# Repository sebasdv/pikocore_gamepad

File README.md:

# pikocore — RP2350-PiZero + GamePi13 port

A community port of [pikocore](https://github.com/schollz/pikocore), the hackable
open-source lo-fi sampler, to run on the **Waveshare RP2350-PiZero** paired with the
**GamePi13** handheld HAT — trading the original's bare-bones potentiometer interface
for a 240×240 color LCD dashboard and a 12-button game-console layout.

This is an independent fork, not officially affiliated with the original pikocore
project or with Waveshare.

## What's different from stock pikocore

- **Full-color 240×240 LCD dashboard** — BPM, clock source, sample name/index,
  live waveform with playhead and per-slice highlighting, the active parameter's
  value as a segmented bar, and the current mode.
- **12 physical buttons** (D-pad + Y/X/B/A + Select/Start/L/R) replace the original's
  8 buttons + 3 potentiometers, with a full on-screen menu system to reach every
  parameter without needing analog knobs.
- **Save/Load device state to flash** — one persisted slot covering every parameter,
  the sequencer pattern, and each mode's own knob position, with on-screen
  save/load confirmation icons.
- **Onboard step sequencer** with visible record/play/clear feedback instead of a
  blind knob.
- **USB bank-loader web app** (React + Vite, in `web/`) to build `.pikobank` files
  from your own samples and load them straight over USB.
- **MIDI clock and transport over USB** — start, stop, continue and clock from a
  computer or phone sync the sequencer, in either clock-input mode.
- microSD `.pikobank` browsing exists in the codebase but ships **disabled by
  default** behind a build flag (`PIKO_GAMEPI13_SD`) — see
  [GAMEPI13-INTERFACE.md](GAMEPI13-INTERFACE.md) for why.

All of the original pikocore's audio engine — sample playback, slicing, retrigger/
stutter, probability-driven jump/gate/reverse/tunnel effects, filter, timestretch —
is untouched; this port only adds the screen, the button-driven menu, and the
persistence layer around it.

## Hardware

- [Waveshare RP2350-PiZero](https://www.waveshare.com/wiki/RP2350-PiZero) —
  RP2350B, dual Cortex-M33/Hazard3, 520KB SRAM, 16MB flash, Pi Zero form factor.
- [Waveshare GamePi13](https://www.waveshare.com/wiki/GamePi13) — 1.3" 240×240
  ST7789 LCD, 12-button handheld HAT, onboard speaker/headphone jack.
- microSD card (optional, FAT32) — only needed if you rebuild with
  `PIKO_GAMEPI13_SD=ON`.

## Building

```
mkdir -p build-gamepi && cd build-gamepi
cmake -DPICO_SDK_PATH=../pico-sdk -DPIKO_GAMEPI13=ON ..
make -j4
```

Flash `build-gamepi/pikocore.uf2` (hold BOOTSEL while plugging in USB).

The original, unmodified stock-hardware build (potentiometers, no LCD) still works
from the same tree — see the [upstream build instructions](#upstream-pikocore) below.
The custom carrier-PCB variant (RP2350-Plus + I2S DAC) builds with
`-DPIKO_GAMEPAD=ON` instead — see [hardware/pikocore_gamepad/README.md](hardware/pikocore_gamepad/README.md).

## Loading samples

Use the loader at **[sebasdv.github.io/pikocore_gamepad](https://sebasdv.github.io/pikocore_gamepad/)**
— no local server needed, just open it in a browser that supports Web Serial
(Chrome/Edge).

Build a bank from your own samples and either load it straight over USB, or use
the "Download bank" button to produce a `.pikobank` file for a microSD card (if
built with SD support).

To run the loader locally instead (e.g. for development):

```
cd web && npm install && npm run dev
```

## Controls

| Control | Function |
|---|---|
| D-pad + Y/X/B/A | pikocore's 8 music buttons |
| Select | cycle parameter mode (tap), or hold + a music button to jump directly to that mode |
| L / R | decrease/increase the active parameter (Function A); hold to repeat |
| Start (tap) | mute / start-stop |
| Start (hold) + L/R | edit Function B instead of Function A |
| Up+Down+B+A | reset FX (filter, distortion, all probabilities) |
| Down+Left+X+B | toggle clock lock |

Full mode table, per-button behavior, retrigger mechanics, and every hardware
finding from bring-up are in [GAMEPI13-INTERFACE.md](GAMEPI13-INTERFACE.md)
(Spanish). Build/flash/pinout quick reference:
[README-GAMEPI13.md](README-GAMEPI13.md) (Spanish).

## Upstream pikocore

For the original potentiometer-based hardware, schematic, BOM, and firmware
releases, see the upstream project:

- [Website](https://pikocore.com)
- [Source code](https://github.com/schollz/pikocore)
- [Schematic](https://infinitedigits.co/img/pikocore_schematic.png)
- [BOM](https://infinitedigits.co/wares/pikocore/#bom)
- [Video demonstration](https://www.youtube.com/watch?v=mKPq1Chm9Tg)

```
SAMPLE_RATE=31000 make
```

(`make build2` if you're on a 2MB Pico; the default targets 16MB.) See the
upstream README for the full prerequisites list (`make prereqs`).

## Acknowledgments

This port stands entirely on other people's work:

- **[Zack Scholl](https://github.com/schollz)** ([infinitedigits.co](https://infinitedigits.co)) —
  created [pikocore](https://github.com/schollz/pikocore), the sampler engine this
  whole project is built on. pikocore is the deliberately minimal, cheap sibling of
  his larger [zeptocore](https://github.com/schollz/_core) sampler; both descend
  from the same `_core` lineage.
- **[Waveshare](https://www.waveshare.com/)** — designed the
  [RP2350-PiZero](https://www.waveshare.com/wiki/RP2350-PiZero) board and the
  [GamePi13](https://www.waveshare.com/wiki/GamePi13) HAT this port targets. The
  vendored LCD driver (`src/gamepi13/lcd/`) and board files
  (`RP2350-PiZero/`, `Gamepi13-RP2040-Demo/`) are adapted from Waveshare's own demo
  code for this hardware.
- **[Raspberry Pi Foundation](https://github.com/raspberrypi/pico-sdk)** — the
  Pico SDK this firmware (and the RP2350) builds on.
- **[carlk3](https://github.com/carlk3/no-OS-FatFS-SD-SDIO-SPI-RPi-Pico)** — the
  microSD FatFS driver used for the (currently parked) SD bank-browsing mode,
  itself built on **ChaN's [FatFs](http://elm-chan.org/fsw/ff/00index_e.html)**, an
  SPI block-device driver derived from Mbed OS 5's `SDBlockDevice`, and an SDIO
  driver derived from [ZuluSCSI-firmware](https://github.com/ZuluSCSI/ZuluSCSI-firmware).
- **Raspberry Pi (Trading) Ltd** and **ForsakenNGS** — the WS2812 driver
  (`doth/WS2812.cpp`), inherited from upstream pikocore under its original
  BSD-3-Clause / GPL-3 dual attribution (see the file header).
- **andrewikenberry** and **[Jacob Vosmaer](https://github.com/jvosmaer)** — the
  one-wire MIDI implementation (`doth/onewiremidi.h`), MIT licensed, inherited from
  upstream pikocore.
- **[ittybittymidi](https://ittybittymidi.com)** — the MIDI clock-in hardware
  pikocore's `MIDI_IN_ENABLED` build option targets.
- **[Lopaka](https://lopaka.app)** — the pixel-art tool used to design every LCD
  UI bitmap in this port (digits, mode labels, icons, splash screen).

## License

MIT — see [LICENSE](LICENSE). Some vendored third-party components carry their
own licenses; see the file headers under `doth/` and the Acknowledgments section
above.

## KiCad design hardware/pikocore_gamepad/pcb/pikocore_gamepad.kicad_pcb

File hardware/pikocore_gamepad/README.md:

# pikocore_gamepad

A new, independent handheld sampler/mangler — same purpose as the pikocore port in
this repo's root, but built from scratch around the **Waveshare RP2350-Plus** core
module with its own carrier PCB, not the RP2350-PiZero + GamePi13 HAT the rest of
this repo targets.

- **Hardware design & BOM:** [`docs/superpowers/specs/2026-08-11-pikocore-gamepad-hardware-design.md`](../../docs/superpowers/specs/2026-08-11-pikocore-gamepad-hardware-design.md)
- **GPIO pin map (source of truth: `pcb/pinmap.py`):** [`docs/hardware/pikocore_gamepad-pinout.md`](../../docs/hardware/pikocore_gamepad-pinout.md)
- **PCB pipeline plan & execution notes:** [`docs/superpowers/plans/2026-08-11-pikocore-gamepad-pcb-fork.md`](../../docs/superpowers/plans/2026-08-11-pikocore-gamepad-pcb-fork.md)
- **NAV5 D-pad + speaker relocation (later layout change):** [`docs/superpowers/specs/2026-08-11-pikocore-gamepad-nav5-speaker-reloc-design.md`](../../docs/superpowers/specs/2026-08-11-pikocore-gamepad-nav5-speaker-reloc-design.md) · [plan](../../docs/superpowers/plans/2026-08-11-pikocore-gamepad-nav5-speaker-reloc.md)

## Firmware target — `PIKO_GAMEPAD=ON`

```
mkdir -p build-gamepad && cd build-gamepad
cmake -DPICO_SDK_PATH=../pico-sdk -DPIKO_GAMEPAD=ON ..
make -j4
```

`PICO_BOARD` becomes `waveshare_rp2350_plus_16mb` (from the Pico SDK). The flag
reuses the whole GamePi13 port (12-button input layer, LCD UI, USB bank loader)
and swaps only what the carrier PCB changes:

- **Pins:** [`src/boards/pikocore_gamepad/config.h`](../../src/boards/pikocore_gamepad/config.h)
  (`PIN_*`, generated by hand from `pcb/pinmap.py`, kept in sync by gate G-4) mapped
  onto the shared `GAMEPI_*` names in `src/hw_gamepi13.h`. All 12 buttons use
  `gpio_pull_up()`; the D-pad is four discrete tacts (SW1–SW4).
- **Audio:** I2S to the PCM5102A over PIO0 (`src/gamepad/i2s.pio`,
  `src/gamepad/audio_i2s.h`), BCK GP16 / LRCK GP17 / DIN GP8 at 48 kHz. The
  audio engine still ticks off a PWM slice (slice 0, no GPIO routed) exactly as the
  PWM build does; a DMA channel in endless mode zero-order-holds its latest sample
  into the I2S FIFO. `DAC_XSMT` (GP22) stays low until clocks run and the first
  samples are out, then goes high. `SPK_SHDN` (GP20) follows `JACK_DET` (GP21,
  pull-up): plug in = speaker off.
- **LCD:** same vendored ST7789 driver on SPI0 (SCK GP2, MOSI GP3, DC GP5, RES GP6,
  BLK GP7 PWM straight to the module's BLK pin, 1 = on). The display is the 1.3"
  240x240 IPS module with a 7-pin header; it has no CS line (tied to GND on the
  module: `GAMEPI_LCD_CS_PIN -1`, skipped in `dev_shim.c`) and no TE pin, so GP26
  is free.
- **MIDI:** over the module's USB-C only. The board has no MIDI jacks since
  2026-11-05, so GP27 and GP28 are free and the one-wire receiver is not created.
- **Not built:** microSD (no socket; mode 8 stays unreachable, FatFs is not linked)
  and the HDMI mirror. `PIKO_GAMEPI13=ON` keeps building unchanged.

**Not bench-tested.** There is no assembled board yet: the target compiles, gate
G-4 passes, and the I2S/mute/jack sequencing follows the PCM5102A and PAM8302A
datasheets, but nothing above has run on hardware. First things to check on a
real board: DAC lock and unmute click, speaker/jack switching, the LCD SPI clock
(`GAMEPI_LCD_SPI_HZ`, left at the GamePi13's 10 MHz), and button polarity.

## `pcb/`

A scriptable KiCad generation pipeline (Python: `pinmap.py`, `netlist.py`,
`gen_sch.py`, `gen_pcb.py`, `checks/`), forked and adapted from a sibling project
(`GAMESETUP`) that targets the same RP2350-Plus module.

**Current state (layout of 2026-10-17, MIDI jacks removed on 2026-11-05):** **100 × 60 mm**,
4 layers, 66 parts: the Micro layout on the RP2350-Plus module
([spec](../../docs/superpowers/specs/2026-10-16-pikocore-gamepad-module-micro-midi-design.md)),
with the display switched to the 1.3" 240x240 ST7789 IPS module with a 7-pin
2.54 mm header ([spec](../../docs/superpowers/specs/2026-10-17-pantalla-7-pines-design.md)).
MIDI goes over the module's USB-C
([spec](../../docs/superpowers/specs/2026-11-05-usb-midi-audio-design.md)): the
two TRS jacks and their circuit (J6, J7, U9, U10, R40–R43, D3, C56) left the
board on 2026-11-05, GP27 and GP28 are free, and no other part moved.
The module (J4, 27.78 × 39.22 per the manufacturer's drawing) sits on the front
over its header, pins soldered by hand, pin row at the top; D-pad and X/Y/A/B on either side, Select/Start at the lower right,
triggers in the top corners. It carries its own backlight driver: `LCD_BLK` (GP7) goes straight to
its BLK pin. On the back the RP2350-Plus is **soldered flat by its castellated
edges** (footprint `RP2350-Plus_Castellated`) at (50, 33) with its USB-C at the
bottom edge. The phones jack is on the left edge. Hand copper: the boost loop
only. Gates: 221 tests OK; `run_all.py` exit 0
with every gate green, G-0 included ("all physical constants and footprints are
verified"), plus G-5/G-4 (23 pins)/G-2 (215 connections)/placement; ERC 0; DRC 0
errors, 0 unconnected, 0 parity mismatches, 11 warnings (silkscreen, and a
library mismatch on SW9/SW10). `gen_fab.py` without `--force` writes
`pikocore_gamepad_fab.zip` (155 KB, no NO-FABRICABLE suffix; 38 BOM lines, 17
without LCSC; 47 SMD in the CPL) and G-F reports everything up to date. The 17
lines without LCSC are parts the user buys and solders or places by hand (12
tacts, the phones jack, the speaker, the two 470 uF, U1 and J4); U1 and
J4 are not in the CPL. Those 18 parts carry their reference designator on the
silkscreen of their side, to find their place when assembling; every other
reference stays on the Fab layers, which are not printed. The three 22 uF (C5, C6, C28) use LCSC C602037, the same
Samsung series as C45783, which had no stock on 2026-11-05; C602037 may be
charged as an Extended part (up to US$3.07 per order), so switch back to
C45783 if it restocks before ordering. Gates passing is not the same as a board built or
checked: see the open items below. The DXF template (100 × 60) now carries J4 with its full module
outline, for the enclosure window. The display module has no 3D model, so it
does not appear in renders (the user's STEP, `pcb/1.3 Inch 1.3.step`, is in
the repo but not wired to J4). No board has been built.

**Why not the cheaper RP2040-Plus 16MB (evaluated 2026-11-04):** same Pico
footprint, pinout and battery header, US$1-2 less, but it does not fit. The
firmware runs from RAM (`copy_to_ram`, inherited from upstream pikocore): the
`PIKO_GAMEPAD` build configured with `-DPICO_BOARD=waveshare_rp2040_plus_16mb`
compiles, but the link needs 392 860 B of RAM against the RP2040's 262 144 B
main region (overflow of 130 716 B; code plus constants alone are 249 KB, so
even dropping the 115 KB framebuffer would not do). It only links as an XIP
build (151 092 B of RAM), and that is a port, not a board swap: audio ISR at
~1 MHz from the 16 KB XIP cache, flash writes during USB sample loading with
core 1 running from flash, and `src/gamepad/audio_i2s.h` uses the RP2350-only
DMA ENDLESS mode (an RP2040 needs two chained channels). The RP2350-Plus stays.

The user measured the module in hand and confirmed on 2026-10-17
`LCD7_PIN_ROW_TO_EDGE` = 1.27 mm and `LCD7_PIN_DRILL` = 1.0 mm; both are
`verified=True` in `pcb/params.py`, which is why G-0 is green.

Orientation: screen up, header row at the top, the leftmost label must read
GND and goes into the square pad (the board has GND/BLK silk labels). A wrong
orientation swaps GND/BLK, 3V3/DC and SCK/RES. The user's photo of the module
(2026-10-17) shows exactly this order (GND VCC SCL SDA RES DC BLK, left to
right, header on top, GND on the square pad), and the user confirmed on
2026-10-17 that the part in hand is the one in the photo: orientation is
closed.

Not verified (no gate covers it): the Plus's castellation pad pattern against
the Pico footprint (the user confirmed on 2026-10-17 that they are identical)
but not that its underside is flat so it sits on the board; the module's
battery connector against the user's JST GH cells (the carrier cannot reach the
module's battery line, so the cells need a GH-to-MX1.25 pigtail or a re-crimped
plug); MIDI over USB (firmware, never run on hardware); the BLK polarity and
pull state
of the display module (firmware assumes active-high); an optional 1 uF at J4
pin 2; the enclosure. When ordering, JLCPCB must be told not to assemble U1 and
J4 and not to paste U1's B.Paste-only openings.

To reproduce the board, `bash pcb/route_cycle.sh` regenerates schematic, netlist
and board from scratch (`gen_pcb.py` calls `NewBoard()`: GUI edits and the
previous routing are discarded) and re-routes with freerouting 2.5.0, with its
fanout stage off (it put vias against U1's hand-soldered pads); edit the JAR
path at the top of the script for your machine.

**History:** this layout reached `main` on 2026-11-04 through PR #3 (module
soldered flat, Micro layout, MIDI) and PR #4 (7-pin display module); the MIDI
jacks left it on 2026-11-05 (branch `hw/sin-jacks-midi`). Earlier
variants live in the history: the same board with the two MIDI jacks (`main`
before the `hw/sin-jacks-midi` merge), the same board with the bare 24-pin panel on a
flex (`hw/modulo-micro-midi` before PR #4 was merged into it), the 100 × 80 mm
board with the RP2350-Plus on a socket (`main` before merge `572ca8a`), and
the chip-down RP2350A board (branch `hw/chipdown-rp2350`, PR #2, kept as
reference).

`PARTES.md` and `PENDIENTES.md` inside `pcb/` are inherited from GAMESETUP and
describe *that* project, not this one — kept for the component research they
contain (verified footprints, part-sourcing decisions), marked historical at the
top of each file.

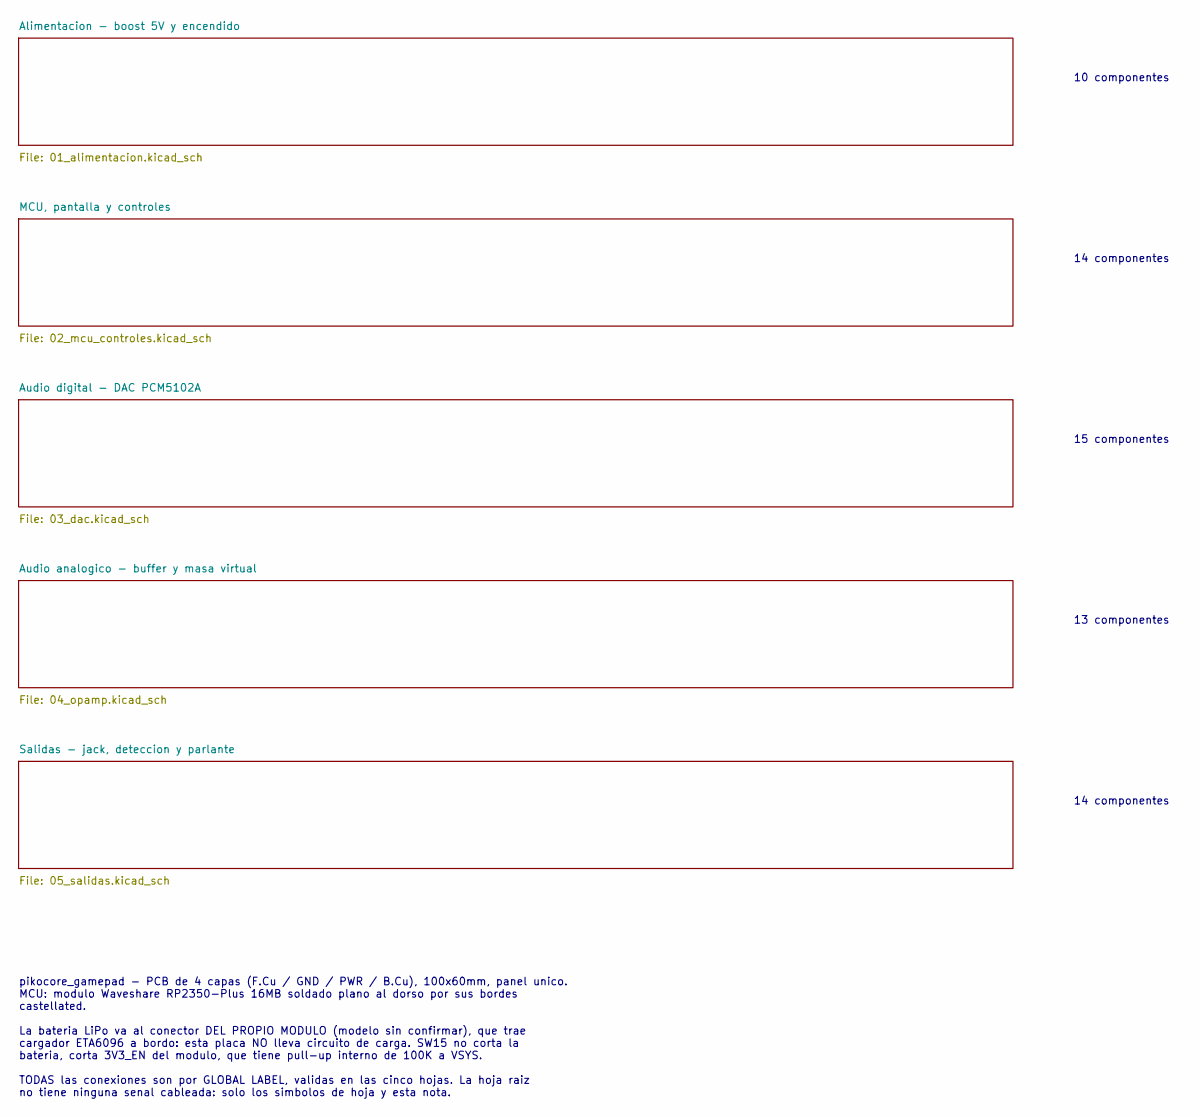
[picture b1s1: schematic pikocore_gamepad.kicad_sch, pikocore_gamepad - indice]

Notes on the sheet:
10 componentes
14 componentes
15 componentes
13 componentes
pikocore_gamepad - PCB de 4 capas (F.Cu / GND / PWR / B.Cu), 100x60mm, panel unico. MCU: modulo Waveshare RP2350-Plus 16MB soldado plano al dorso por sus bordes castellated. La bateria LiPo va al conector DEL PROPIO MODULO (modelo sin confirmar), que trae cargador ETA6096 a bordo: esta placa NO lle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

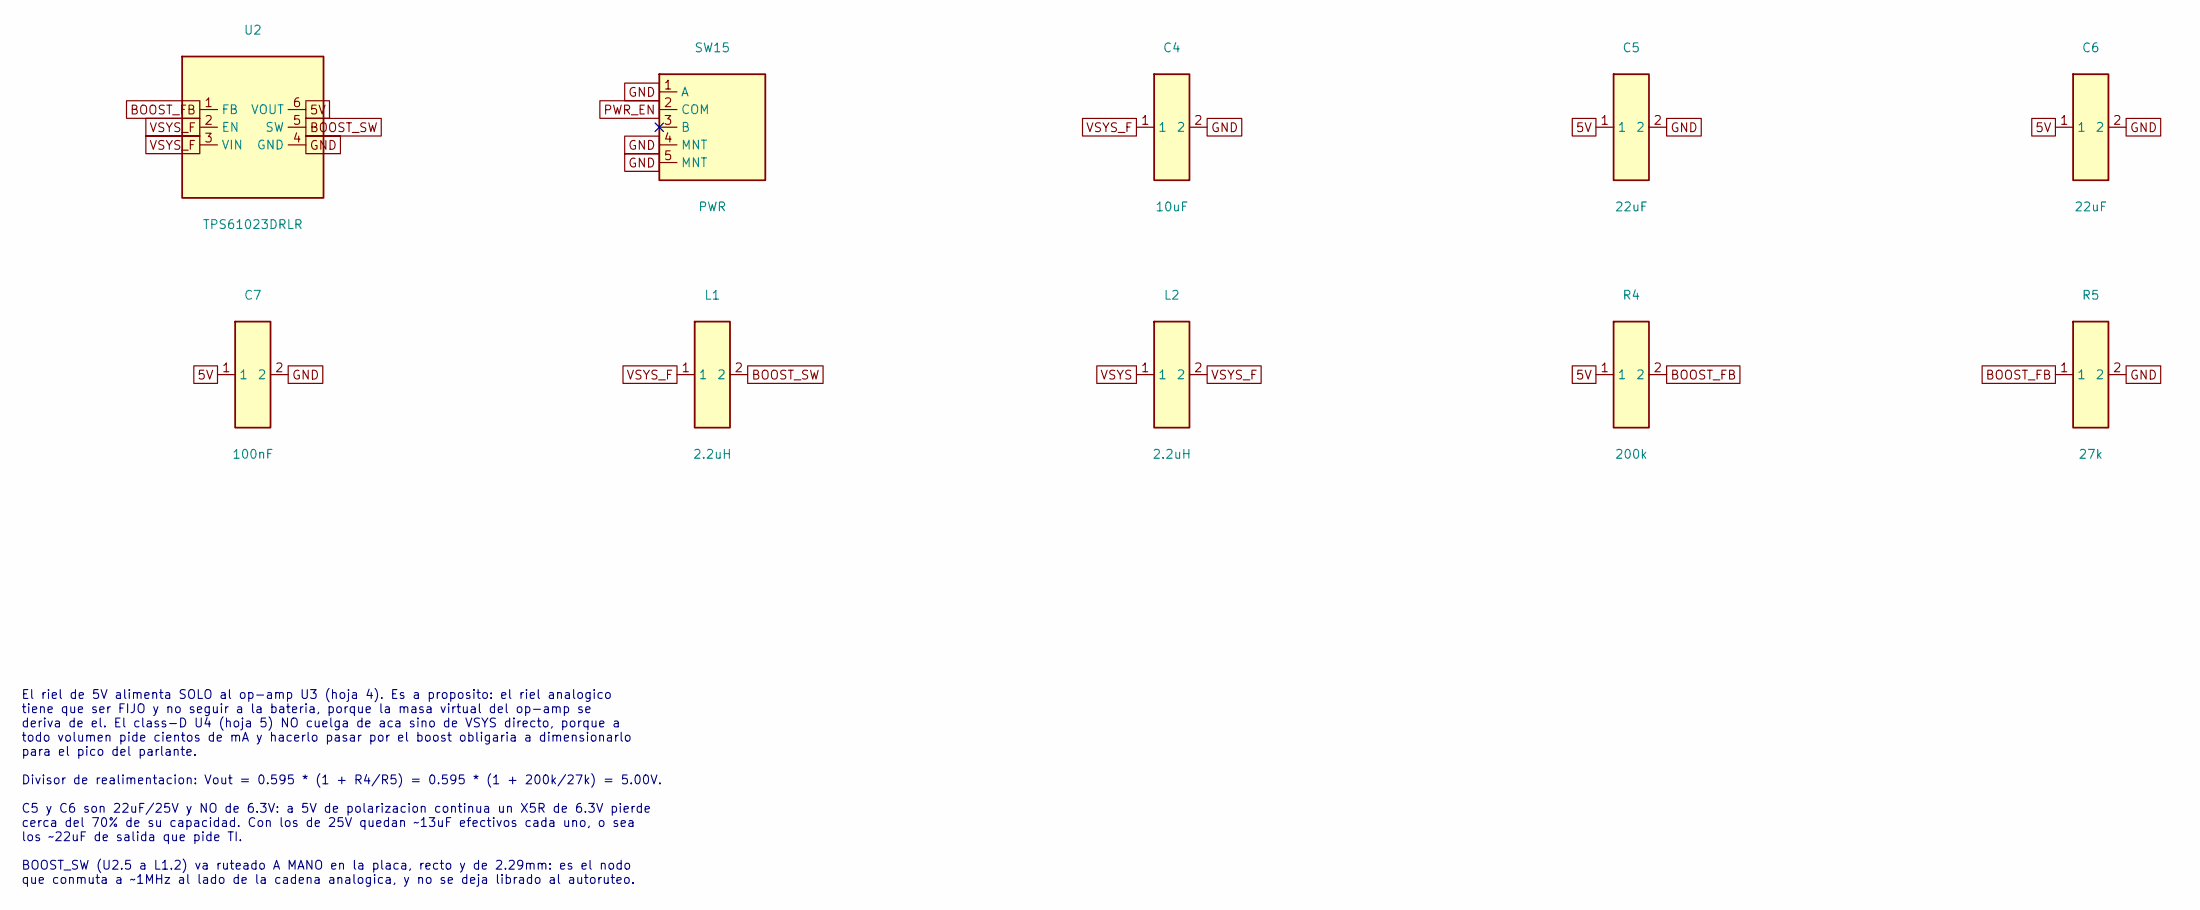
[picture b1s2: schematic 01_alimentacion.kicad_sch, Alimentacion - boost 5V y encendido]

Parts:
C4: 10uF; C_0603_1608Metric; LCSC C19702
C5, C6: 22uF; C_0805_2012Metric; LCSC C602037
C7: 100nF; C_0603_1608Metric; LCSC C14663
L1, L2: 2.2uH; L_1210_3225Metric; LCSC C3002559
R4: 200k; R_0603_1608Metric; LCSC C25811
R5: 27k; R_0603_1608Metric; LCSC C22967
SW15: PWR; SW-TH_SK12D07VG3; LCSC C431547
U2: TPS61023DRLR; SOT-563; LCSC C919459

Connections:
5V: C5.1, C6.1, C7.1, R4.1, U2.6 (VOUT); also elsewhere on the board
BOOST_FB: R4.2, R5.1, U2.1 (FB)
BOOST_SW: L1.2, U2.5 (SW)
GND: C4.2, C5.2, C6.2, C7.2, R5.2, SW15.1 (A), SW15.4 (MNT), SW15.5 (MNT), U2.4 (GND); also elsewhere on the board
PWR_EN: SW15.2 (COM); also elsewhere on the board
VSYS: L2.1; also elsewhere on the board
VSYS_F: C4.1, L1.1, L2.2, U2.2 (EN), U2.3 (VIN)

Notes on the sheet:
El riel de 5V alimenta SOLO al op-amp U3 (hoja 4). Es a proposito: el riel analogico tiene que ser FIJO y no seguir a la bateria, porque la masa virtual del op-amp se deriva de el. El class-D U4 (hoja 5) NO cuelga de aca sino de VSYS directo, porque a todo volumen pide cientos de mA y hacerlo pasar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

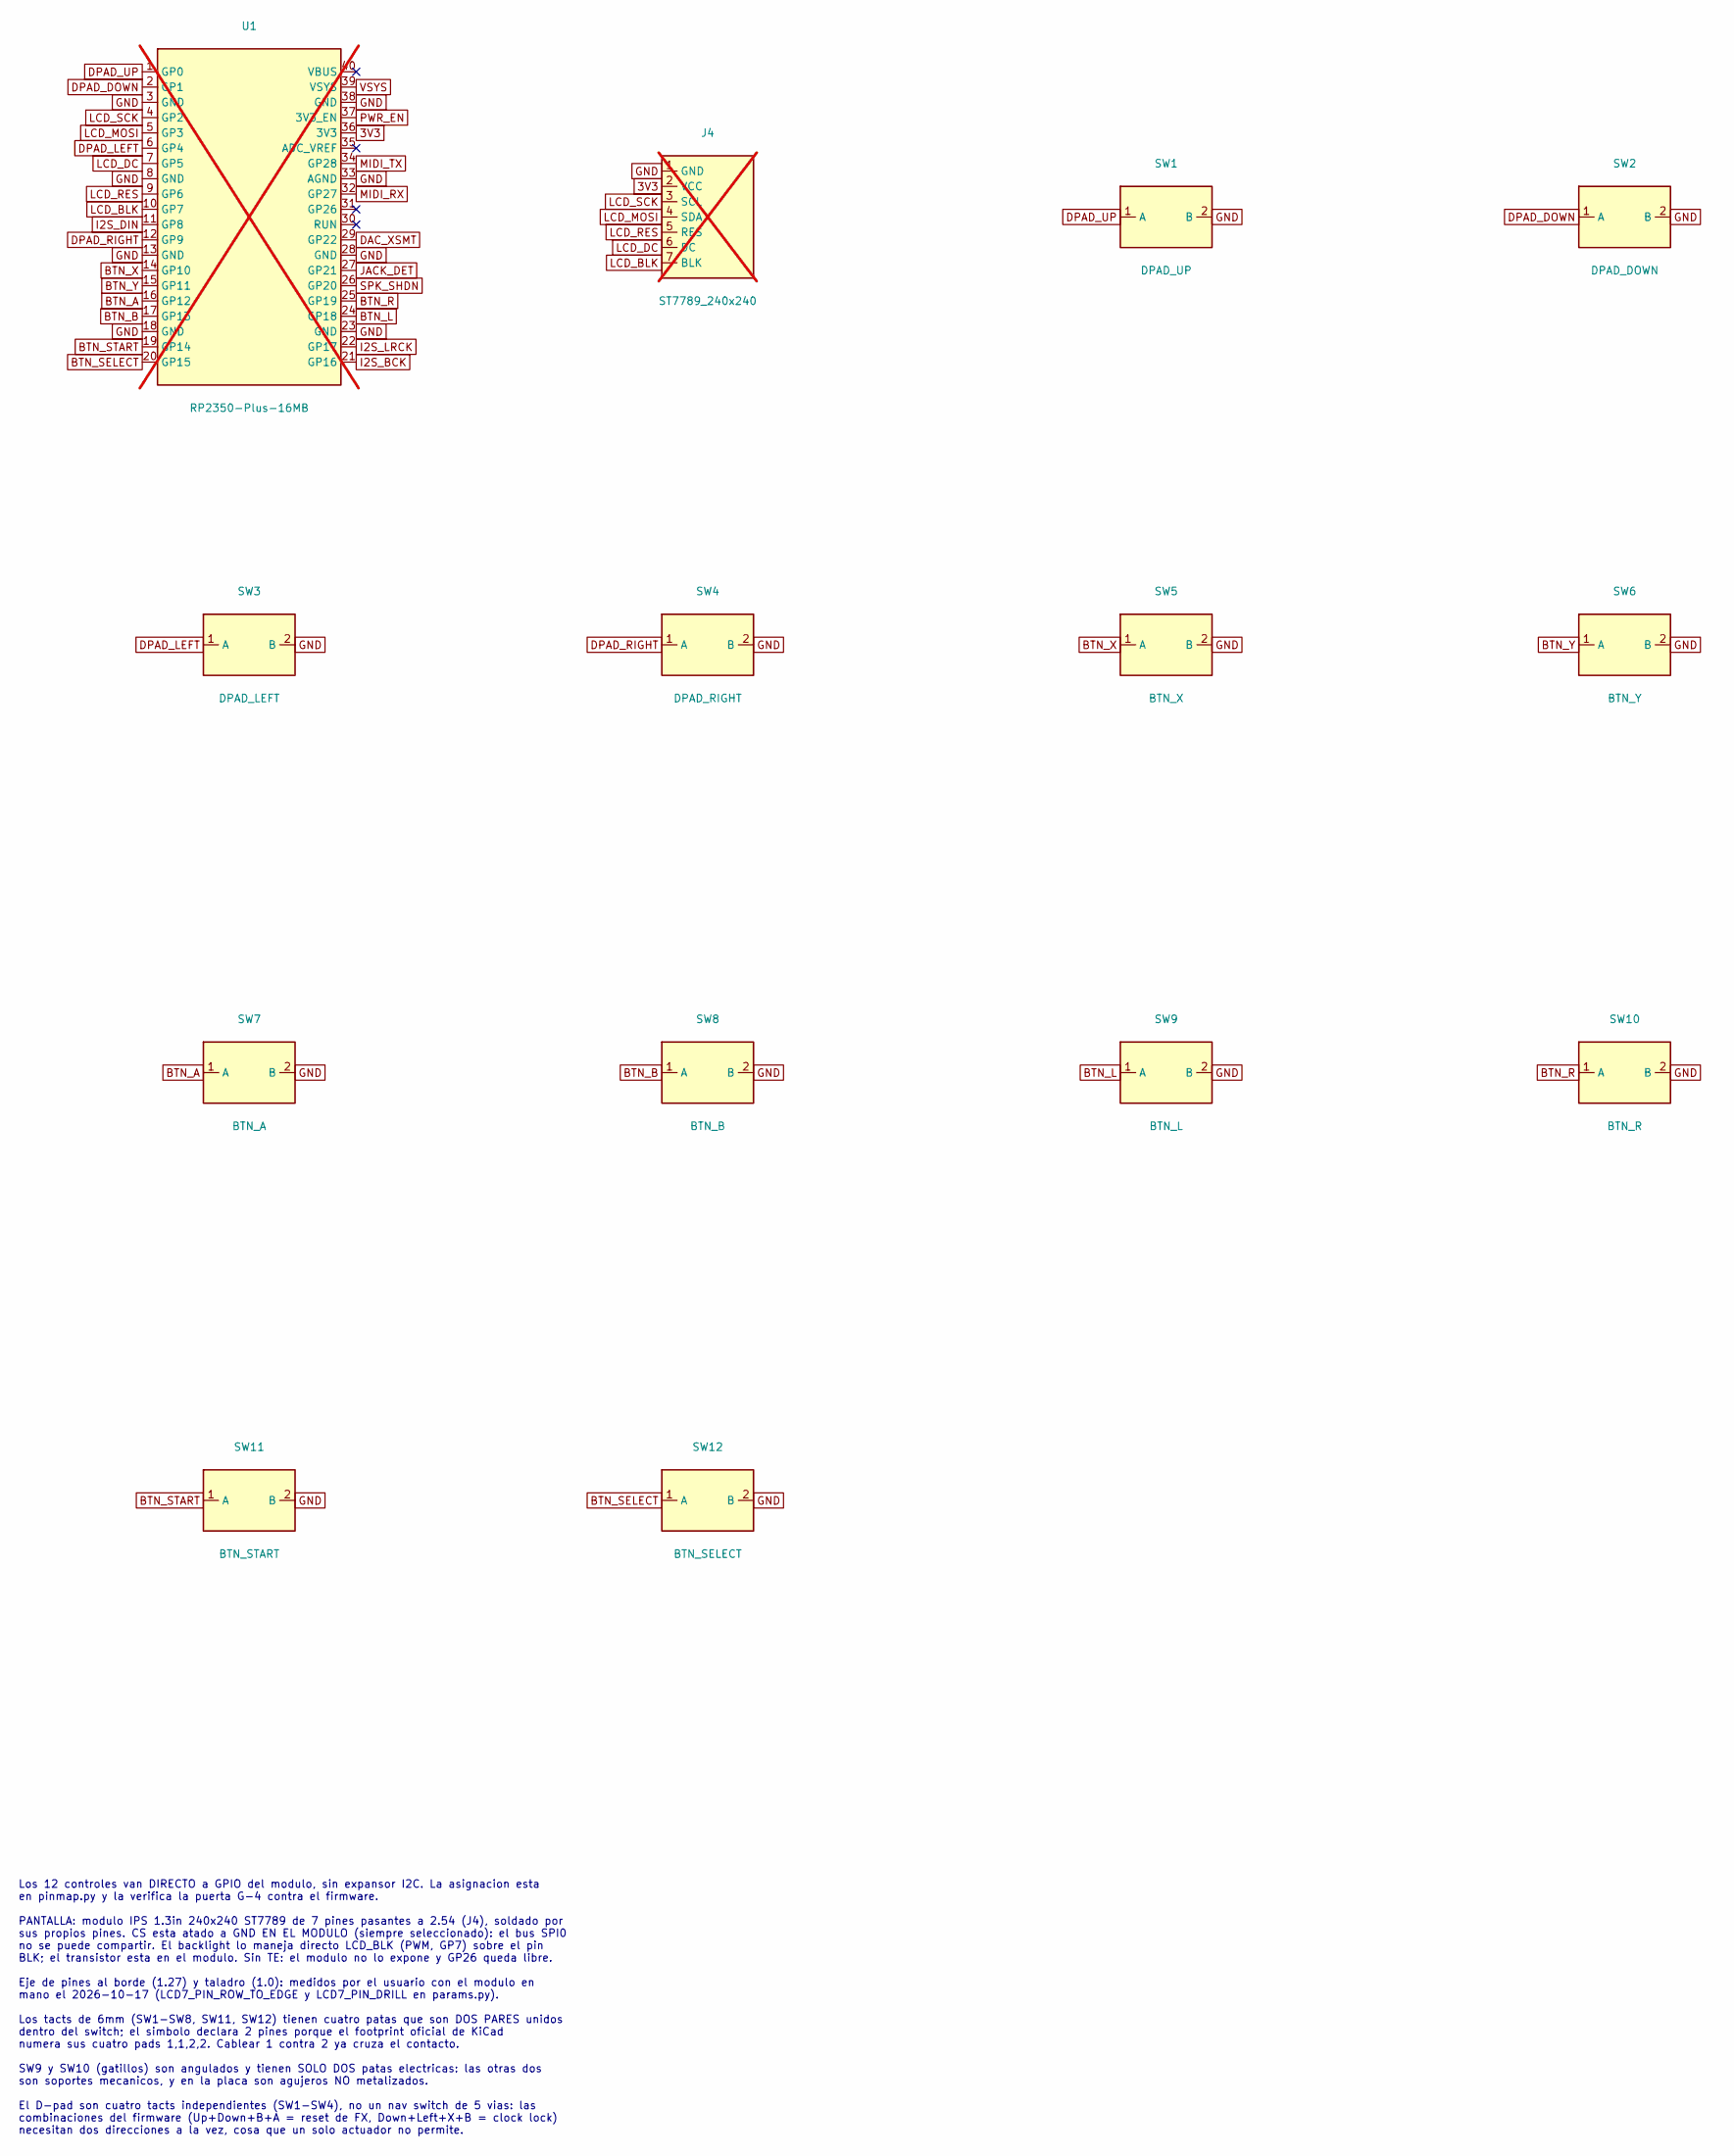
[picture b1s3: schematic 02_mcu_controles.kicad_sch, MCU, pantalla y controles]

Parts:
J4: ST7789_240x240; LCD_ST7789_240x240_7P; not fitted
SW1: DPAD_UP; SW_PUSH_6mm
SW2: DPAD_DOWN; SW_PUSH_6mm
SW3: DPAD_LEFT; SW_PUSH_6mm
SW4: DPAD_RIGHT; SW_PUSH_6mm
SW5: BTN_X; SW_PUSH_6mm
SW6: BTN_Y; SW_PUSH_6mm
SW7: BTN_A; SW_PUSH_6mm
SW8: BTN_B; SW_PUSH_6mm
SW9: BTN_L; SW_Tactile_SPST_Angled_PTS645Vx39-2LFS
SW10: BTN_R; SW_Tactile_SPST_Angled_PTS645Vx39-2LFS
SW11: BTN_START; SW_PUSH_6mm
SW12: BTN_SELECT; SW_PUSH_6mm
U1: RP2350-Plus-16MB; RP2350-Plus_Castellated; not fitted

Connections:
3V3: J4.2 (VCC), U1.36 (3V3); also elsewhere on the board
BTN_A: SW7.1 (A), U1.16 (GP12)
BTN_B: SW8.1 (A), U1.17 (GP13)
BTN_L: SW9.1 (A), U1.24 (GP18)
BTN_R: SW10.1 (A), U1.25 (GP19)
BTN_SELECT: SW12.1 (A), U1.20 (GP15)
BTN_START: SW11.1 (A), U1.19 (GP14)
BTN_X: SW5.1 (A), U1.14 (GP10)
BTN_Y: SW6.1 (A), U1.15 (GP11)
DAC_XSMT: U1.29 (GP22); also elsewhere on the board
DPAD_DOWN: SW2.1 (A), U1.2 (GP1)
DPAD_LEFT: SW3.1 (A), U1.6 (GP4)
DPAD_RIGHT: SW4.1 (A), U1.12 (GP9)
DPAD_UP: SW1.1 (A), U1.1 (GP0)
GND: J4.1 (GND), SW1.2 (B), SW2.2 (B), SW3.2 (B), SW4.2 (B), SW5.2 (B), SW6.2 (B), SW7.2 (B), SW8.2 (B), SW9.2 (B), SW10.2 (B), SW11.2 (B), SW12.2 (B), U1.3 (GND), U1.8 (GND), U1.13 (GND), U1.18 (GND), U1.23 (GND), U1.28 (GND), U1.33 (AGND), U1.38 (GND); also elsewhere on the board
I2S_BCK: U1.21 (GP16); also elsewhere on the board
I2S_DIN: U1.11 (GP8); also elsewhere on the board
I2S_LRCK: U1.22 (GP17); also elsewhere on the board
JACK_DET: U1.27 (GP21); also elsewhere on the board
LCD_BLK: J4.7 (BLK), U1.10 (GP7)
LCD_DC: J4.6 (DC), U1.7 (GP5)
LCD_MOSI: J4.4 (SDA), U1.5 (GP3)
LCD_RES: J4.5 (RES), U1.9 (GP6)
LCD_SCK: J4.3 (SCL), U1.4 (GP2)
PWR_EN: U1.37 (3V3_EN); also elsewhere on the board
SPK_SHDN: U1.26 (GP20); also elsewhere on the board
VSYS: U1.39 (VSYS); also elsewhere on the board

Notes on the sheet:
Los 12 controles van DIRECTO a GPIO del modulo, sin expansor I2C. La asignacion esta en pinmap.py y la verifica la puerta G-4 contra el firmware. PANTALLA: modulo IPS 1.3in 240x240 ST7789 de 7 pines pasantes a 2.54 (J4), soldado por sus propios pines. CS esta atado a GND EN EL MODULO (siempre selec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

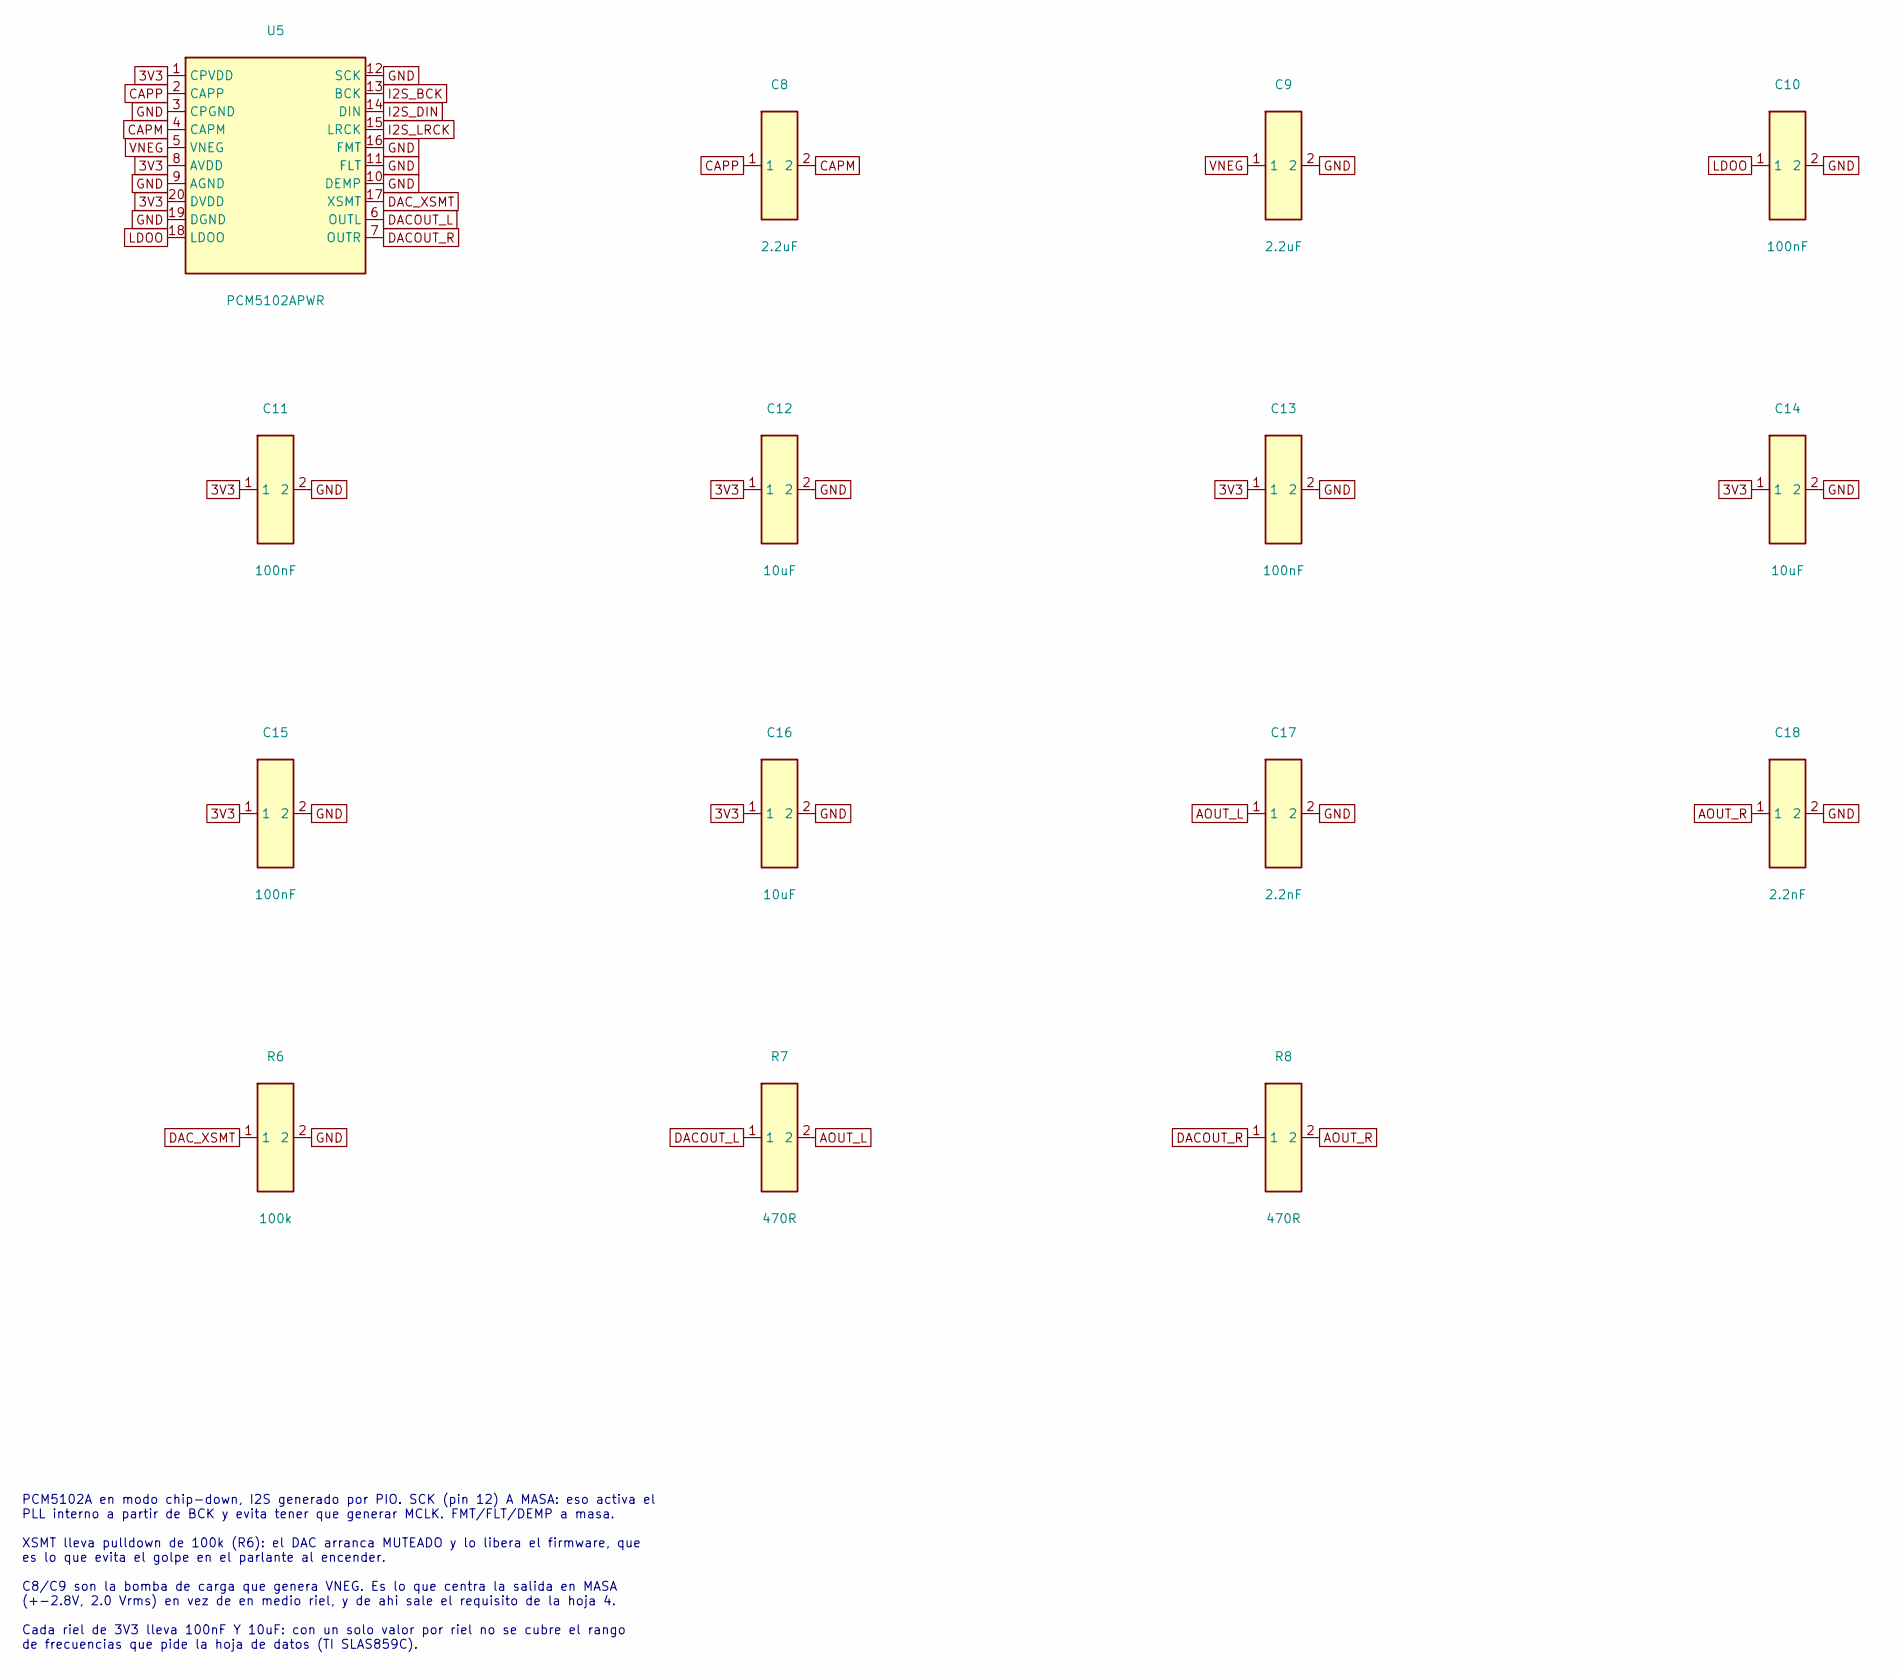
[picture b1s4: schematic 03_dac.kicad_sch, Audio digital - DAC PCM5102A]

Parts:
C8, C9: 2.2uF; C_0603_1608Metric; LCSC C23630
C10, C11, C13, C15: 100nF; C_0603_1608Metric; LCSC C14663
C12, C14, C16: 10uF; C_0603_1608Metric; LCSC C19702
C17, C18: 2.2nF; C_0603_1608Metric; LCSC C1604
R6: 100k; R_0603_1608Metric; LCSC C25803
R7, R8: 470R; R_0603_1608Metric; LCSC C23179
U5: PCM5102APWR; TSSOP-20_L6.5-W4.4-P0.65-LS6.4-BL; LCSC C107671

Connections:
3V3: C11.1, C12.1, C13.1, C14.1, C15.1, C16.1, U5.1 (CPVDD), U5.8 (AVDD), U5.20 (DVDD); also elsewhere on the board
AOUT_L: C17.1, R7.2; also elsewhere on the board
AOUT_R: C18.1, R8.2; also elsewhere on the board
CAPM: C8.2, U5.4 (CAPM)
CAPP: C8.1, U5.2 (CAPP)
DACOUT_L: R7.1, U5.6 (OUTL)
DACOUT_R: R8.1, U5.7 (OUTR)
DAC_XSMT: R6.1, U5.17 (XSMT); also elsewhere on the board
GND: C9.2, C10.2, C11.2, C12.2, C13.2, C14.2, C15.2, C16.2, C17.2, C18.2, R6.2, U5.3 (CPGND), U5.9 (AGND), U5.10 (DEMP), U5.11 (FLT), U5.12 (SCK), U5.16 (FMT), U5.19 (DGND); also elsewhere on the board
I2S_BCK: U5.13 (BCK); also elsewhere on the board
I2S_DIN: U5.14 (DIN); also elsewhere on the board
I2S_LRCK: U5.15 (LRCK); also elsewhere on the board
LDOO: C10.1, U5.18 (LDOO)
VNEG: C9.1, U5.5 (VNEG)

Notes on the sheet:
PCM5102A en modo chip-down, I2S generado por PIO. SCK (pin 12) A MASA: eso activa el PLL interno a partir de BCK y evita tener que generar MCLK. FMT/FLT/DEMP a masa. XSMT lleva pulldown de 100k (R6): el DAC arranca MUTEADO y lo libera el firmware, que es lo que evita el golpe en el parlante al ence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

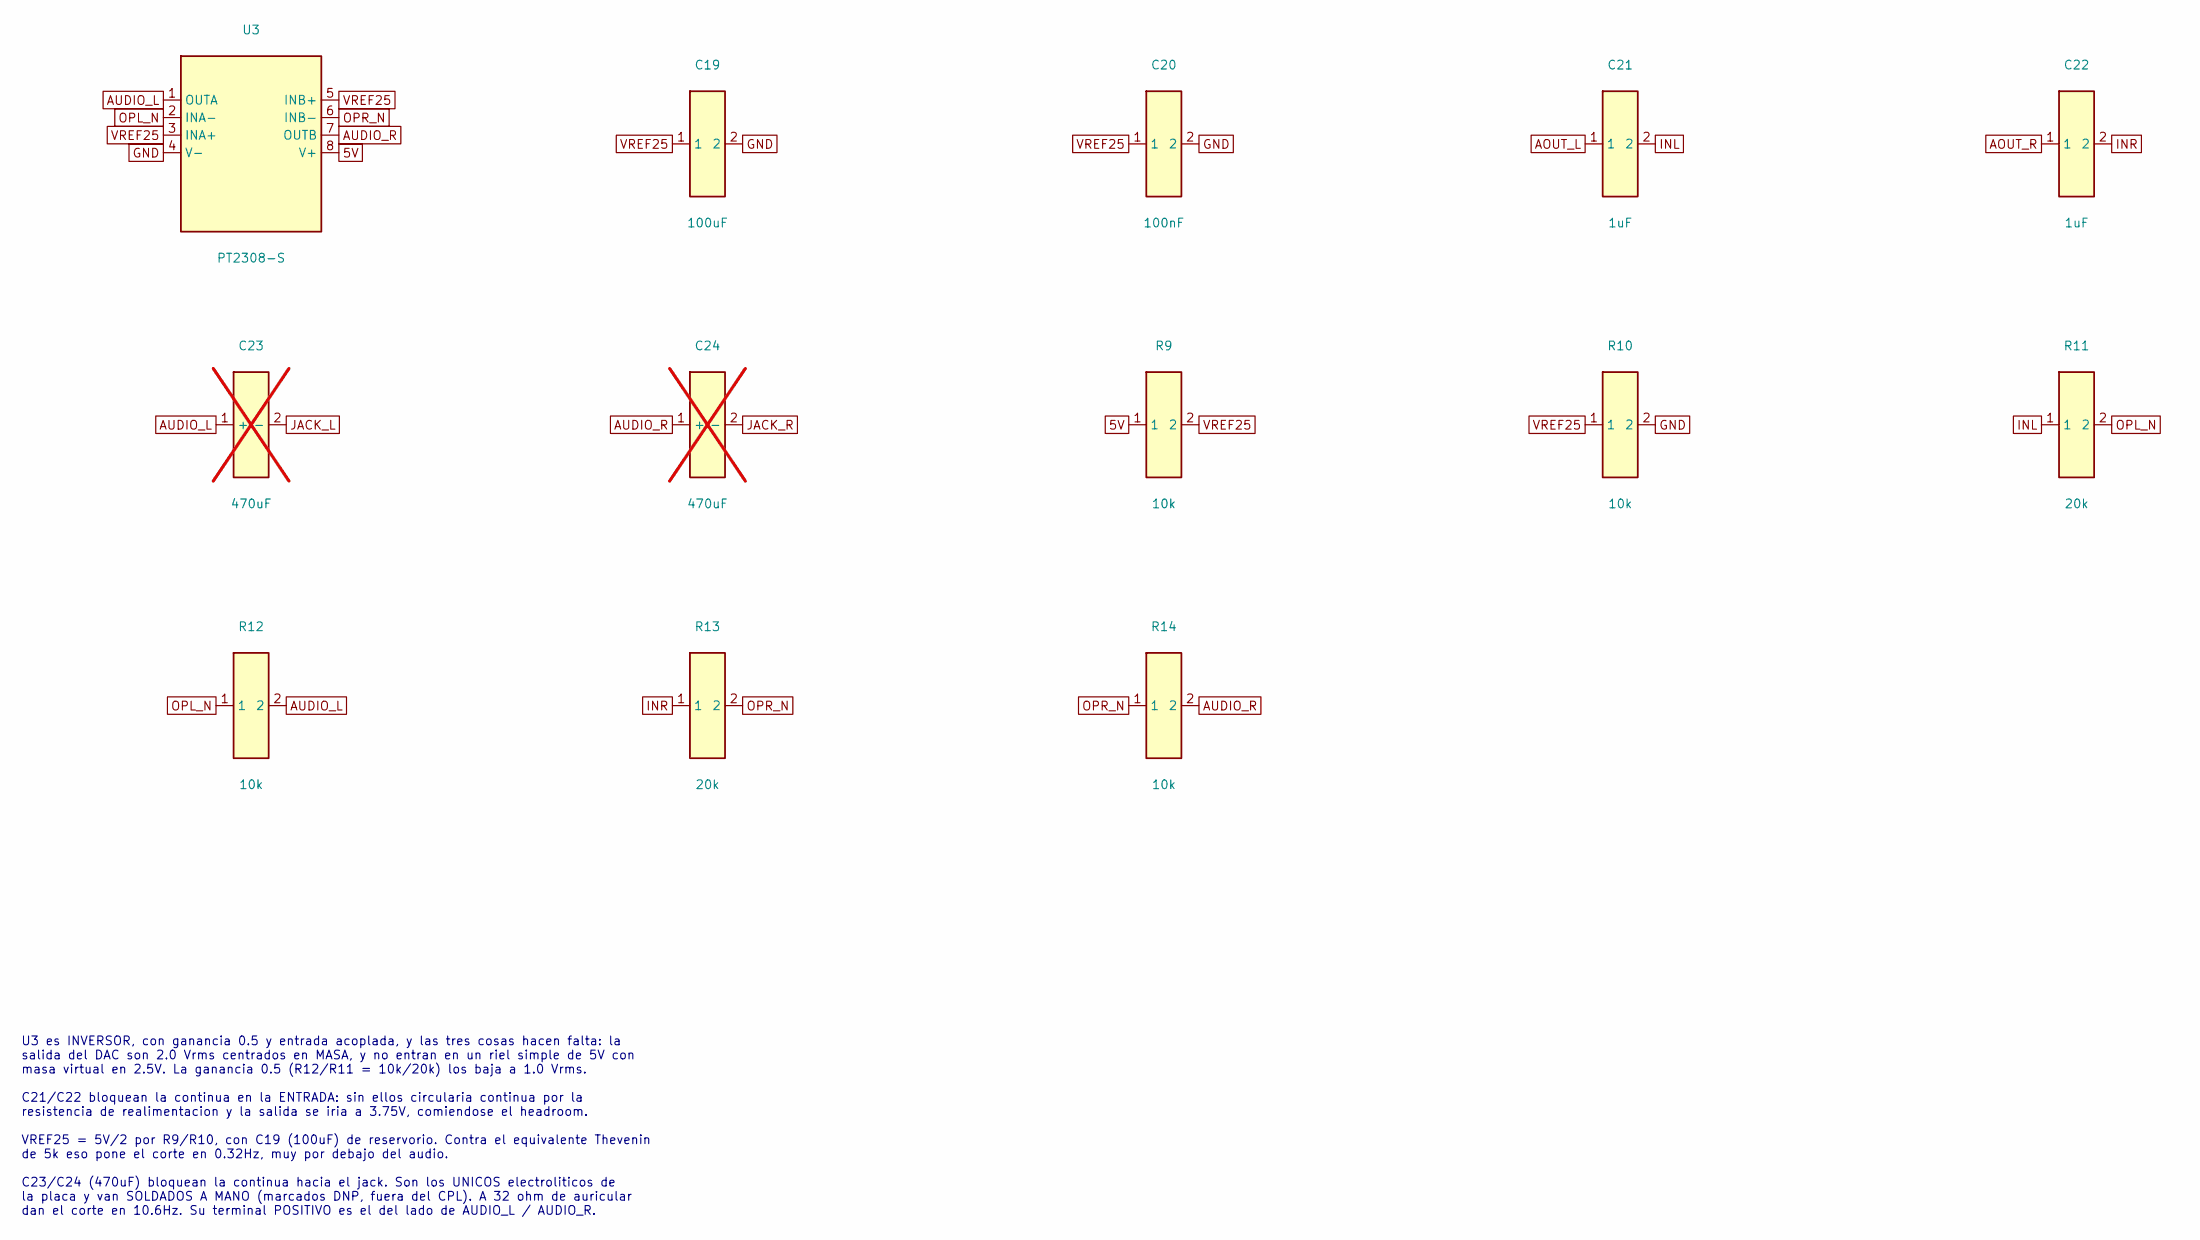
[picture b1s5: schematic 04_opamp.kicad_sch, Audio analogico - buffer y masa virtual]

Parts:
C19: 100uF; C_1206_3216Metric; LCSC C15008
C20: 100nF; C_0603_1608Metric; LCSC C14663
C21, C22: 1uF; C_0603_1608Metric; LCSC C15849
C23, C24: 470uF; CP_Elec_6.3x5.4; not fitted
R9, R10, R12, R14: 10k; R_0603_1608Metric; LCSC C25804
R11, R13: 20k; R_0603_1608Metric; LCSC C4184
U3: PT2308-S; SOIC-8_3.9x4.9mm_P1.27mm; LCSC C115492

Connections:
5V: R9.1, U3.8 (V+); also elsewhere on the board
AOUT_L: C21.1; also elsewhere on the board
AOUT_R: C22.1; also elsewhere on the board
AUDIO_L: C23.1 (+), R12.2, U3.1 (OUTA); also elsewhere on the board
AUDIO_R: C24.1 (+), R14.2, U3.7 (OUTB); also elsewhere on the board
GND: C19.2, C20.2, R10.2, U3.4 (V-); also elsewhere on the board
INL: C21.2, R11.1
INR: C22.2, R13.1
JACK_L: C23.2 (-); also elsewhere on the board
JACK_R: C24.2 (-); also elsewhere on the board
OPL_N: R11.2, R12.1, U3.2 (INA-)
OPR_N: R13.2, R14.1, U3.6 (INB-)
VREF25: C19.1, C20.1, R9.2, R10.1, U3.3 (INA+), U3.5 (INB+)

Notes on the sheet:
U3 es INVERSOR, con ganancia 0.5 y entrada acoplada, y las tres cosas hacen falta: la salida del DAC son 2.0 Vrms centrados en MASA, y no entran en un riel simple de 5V con masa virtual en 2.5V. La ganancia 0.5 (R12/R11 = 10k/20k) los baja a 1.0 Vrms. C21/C22 bloquean la continua en la ENTRADA: sin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
